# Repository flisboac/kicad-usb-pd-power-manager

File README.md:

# USB-PD Power Manager

This is a USB-PD-capable Battery Charger and Power Path Module based on the [HUSB238 USB-PD Sink Controller](https://www.hynetek.com/uploadfiles/site/219/news/aabbbbdb-48c9-4a44-a6dc-2c15f53282e6.pdf) and [BQ25672 Battery Charger](https://www.ti.com/lit/ds/symlink/bq25672.pdf).

> This is **NOT** a finished project!

## Objectives

The main objective with this module is, quite literally, to make the "perfect Power Manager module/solution for any project." Obviously, "perfect" here is what I consider perfect myself, so here goes a laundry list of things I want from it:

1. Actually negotiate power when powered through USB, whatever the means.
    - A lot of projects just depend on the common 5.1K resistor on CC1/CC2 to get 5V/3A, but that's not a guarantee unless your use-case is very restricted.
    - Also, pulling 500mA or more on USB without USB connection/negotiation, USB-PD or USB-BC is out of spec. Not that it matters in all projects, but a well behaved USB-powered solution avoids many surprises.
    - 5V is pretty ubiquitous, but some projects may necessitate more voltage to drive higher-powered devices (e.g. fans), or to charge batteries more efficiently. Higher voltages are also necessary in order for USB-C to deliver more power in general.
2. Capable of negotiating power through **USB PD**, up to the highest power profile available (100W, 20V @ 5A).
    - In the future, I'd like this to be expanded to support USB-PPS as well, but chip availability is a bit low for enabling this functionality, so USB-PD will do for the moment.
3. Capable of falling back to **USB BC**, if not connecting to USB Type-C end-to-end.
    - There's plenty of power available through USB BC 1.2 or similar charger protocols, and it's still very common to use previous USB-A or USB-B (i.e. non Type-C) ports in many places.
4. Battery-powered, with a battery charger built-in.
    - Necessitates Power Path management.
    - Also necessitates battery protection measures, e.g. overcurrent protection, overvoltage protection, reverse polarity protection, etc.
5. Have the smallest possible form-factor. Be friendly to breadboarding, while still being useful as a standalone module.
    - Size would be similar to a Raspberry Pi Pico in width, but no specific restriction on length.
    - Ahem... ✨ [Castellations!](https://jlcpcb.com/blog/castellated-pcbs-introduction-and-design-requirements) ✨ (What a word, ain't it?)
6. Guaranteed 5V and 3.3V outputs, regardless of the "mains" voltage.
    - 5V with a switched dc/dc regulator, for powering sensors, LEDs, etc. Optionally adjustable to 3.3V via standalone (pin) configuration.
    - 3.3V with a LDO for powering microcontrollers, also adjustable to 5V if needed (e.g. for less noise).
    - Both can be disabled at any time, to reduce power consumption.
7. Optional external power input, as a backup for USB power.
8. Battery fuel gauge built-in to the module.
    - Helps with power consumption prediction, etc.
9. I2C as the main control option, but standalone pin or jumper based configuration also possible.
    - Standalone controls enable the board to be used in scenarios without a microcontroller.
    - I2C enables the board to be used with higher precision (e.g. negotiate USB-PD power after first negotiation, configure current/charger limits past the default standalone ones, monitor power consumption, etc.)

I also wanted to put a soft-reset button. I like the idea of the module having power and reset buttons that are useable to a microcontroller, with e.g. long presses meaning turn-off/reset, etc. Perhaps that may be included in a future revision.

## Implementation

### Component selection

Focus on ICs from known brands. Easier to predict availability and quality.

Basic test: go to JLCPCB and see if there's a good amount of stock available. Discard any option with zero stock. Price also important, but not essential (as this will be a personal project).

- USB-PD Sink Controller (**VUSB**): [**HUSB238_002DD**](https://www.hynetek.com/uploadfiles/site/219/news/aabbbbdb-48c9-4a44-a6dc-2c15f53282e6.pdf)
    - 001DD or 004DD would be the best option, but the 002DD has a whole lot more availability for some reason.
    - VUSB is not supposed to be consumed directly, but instead it must be passed on to the Power Path controller.
    - VUSB is only switched on when USB-PD negotiation is performed (either with success or failure).
- Battery Charger and Power Path (**VSYS**): [**BQ25672**](https://www.ti.com/lit/ds/symlink/bq25672.pdf)
    - Selected mostly because of the 24V input voltage tolerance.
    - Having I2C is also important, but not essential.
    - Could be the BQ25792 as well, it's pin-compatible and offers more power, but the BQ25672 has better availability
- Switch-mode DC/DC converter (**VSW**): [**TPS63070**](https://www.ti.com/lit/ds/symlink/tps63070.pdf)
    - Being able to step-up is important for scenarios with 1-cell batteries, or when the input voltage is lower than the output voltage in general. Even more important is to be able to step-down the voltage, considering the upwards of 24V inputs. Hence, it must be a buck-boost.
    - Input comes from VSYS (BQ25672), which reduces the required VIN to 19V.
    - Unfortunately, it has a 16V input voltage limit, but it's the highest limit amongst the moderately available buck-boosts out there. I found no other buck-boost as available or as cheap as this one. If anyone knows of a better option PLEASE let me know, I researched quite a lot but couldn't find a better one!
    - Because of the low VIN input, the module can only be used with up to 3-cell configurations, which limits VSYS to around 13V max. Going above that risks damaging the buck-boost.
- Low-dropout voltage regulator (**VLDO**): [**TPS7A2601**](https://www.ti.com/lit/ds/symlink/tps7a26.pdf)
    - I quite like this LDO!
    - Current limit is a bit low at 500mA, but it's enough for most projects. Higher power can be better served by VBUS or VSW
    - Target output voltages: 3.3V and 5V.
    - Has a very high VIN, at 20V. Safe to connect to VBUS/VSYS, but not exactly safe to use at higher voltages (e.g. regulate from 20V VIN but with much lower output currents in order not to blow it up!)
- MOSFETs: focus on using dual mosfet ICs, in order to reduce board space usage whenever possible.
    - Dual N-Channel: [**Si7224DN**](https://www.mouser.com/datasheet/2/427/si7224dn-1764912.pdf)
        - One of the channels has a lower Vgs, kinda weird. Could have chosen a better one.
    - Dual P-Channel: [**Si7223DN**](https://www.vishay.com/docs/75609/si7223dn.pdf)
    - N-channel and P-channel: [**DMC3025LDV**](https://www.diodes.com/datasheet/download/DMC3025LDV.pdf)
    - Focus on packages compatible with DFN-3x3. Small enough for higher power, whilst being easier to find replacements later on (e.g. chinese options like the HSBB3313, HSBB3909, HSBB6254, HSBB3202, etc.)
    - There were probably better options out there, but I got tired of looking at some point...
- Battery fuel gauge: [**MAX17205G**](https://www.analog.com/media/en/technical-documentation/data-sheets/max17201-max17215.pdf)
    - No particular reason for choosing this one other than the fact that it supports at least 3-cell batteries.
    - Has good performance, low power consumption and enough availability.
    - Useful that it can balance cells as well!

### Module topology

The KiCad schematic focuses on showing the whole module as a single page. I like the idea of being able to see the whole circuit at a glance, obviously separated by smaller logical parts, but this may not be optimal in order to show the constituent parts of the schematic as a whole.

So, follows below a diagram making more evident the constituent parts of the module, I hope it makes sense:

### Schematics

[Schematics PDF here.](/docs/kicad/schematics/toy-usb-pd-power-manager.pdf)

### PCB layout

I stopped working on the PCB layout in order to re-evaluate the project and make a review in general, but all the constituent parts are laid out and routed (with some exceptions). For example, the switch-mode DC/DC converters are laid out according to datasheet suggestions, but are not connected to the overall board.

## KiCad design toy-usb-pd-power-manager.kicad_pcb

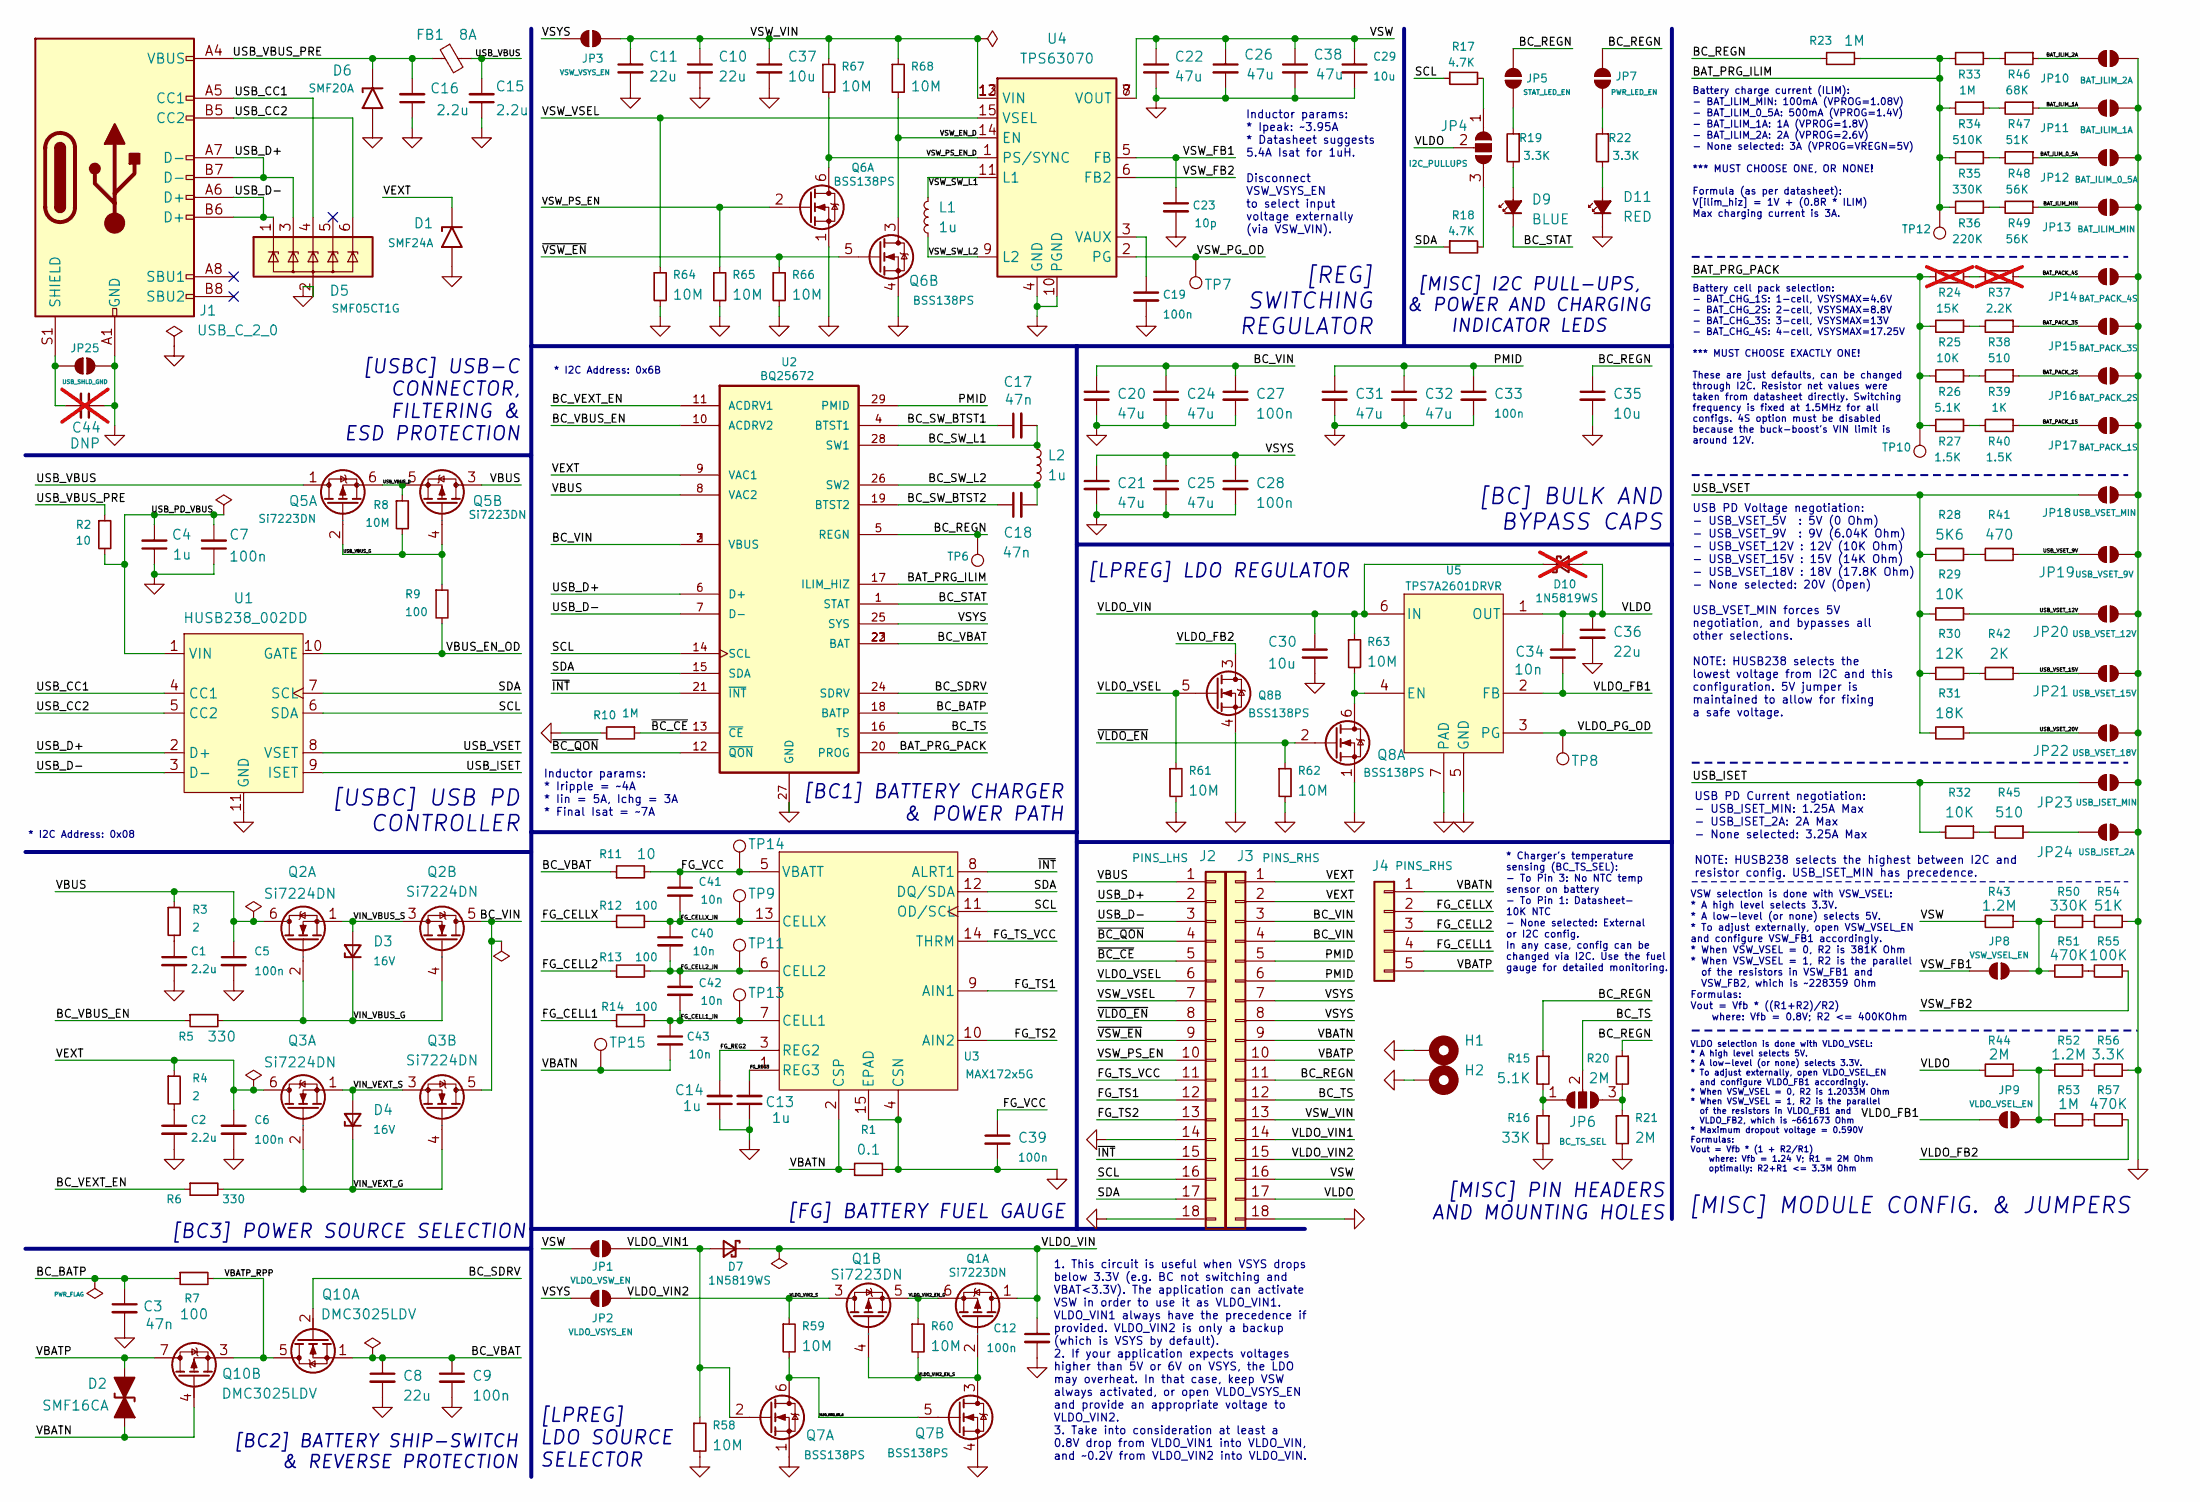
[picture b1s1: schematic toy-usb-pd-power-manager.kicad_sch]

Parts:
C1, C2: 2.2u; C_0805_2012Metric
C3, C17, C18: 47n; C_0402_1005Metric
C4, C13, C14: 1u; C_0402_1005Metric
C5, C6, C7, C9, C12, C19, C27, C28, C33, C39: 100n; C_0402_1005Metric
C8, C10, C11, C36: 22u; C_0805_2012Metric
C15, C16: 2.2u; C_0603_1608Metric
C20, C21, C22, C24, C25, C26, C31, C32, C38: 47u; C_0805_2012Metric
C23: 10p; C_0402_1005Metric
C29, C37: 10u; C_0603_1608Metric
C30, C35: 10u; C_0805_2012Metric
C34, C40, C41, C42, C43: 10n; C_0402_1005Metric
C44: DNP; C_0603_1608Metric; not fitted
D1: SMF24A; D_SMF
D2: SMF16CA; D_SOD-123F
D3, D4: 16V; D_SOD-523
D5: SMF05CT1G; SOT-23-6
D6: SMF20A; D_SMF
D7: 1N5819WS; D_SOD-323
D9: BLUE; LED_0603_1608Metric
D10: 1N5819WS; D_SOD-323; not fitted
D11: RED; LED_0603_1608Metric
FB1: 8A; L_1210_3225Metric
H1, H2: MountingHole_Pad; MountingHole_2.2mm_M2_DIN965_Pad_TopBottom
J1: USB_C_2_0; USB_C_Receptacle_GCT_USB4105-xx-A_16P_TopMnt_Horizontal
J2: PINS_LHS; PinHeader_1x18_P2.54mm_Vertical
J3: PINS_RHS; PinHeader_1x18_P2.54mm_Vertical
J4: PINS_RHS; PinHeader_1x05_P2.54mm_Vertical
JP1: VLDO_VSW_EN; SolderJumper-2_P1.3mm_Open_Pad1.0x1.5mm
JP2: VLDO_VSYS_EN; SolderJumper-2_P1.3mm_Open_Pad1.0x1.5mm
JP3: VSW_VSYS_EN; SolderJumper-2_P1.3mm_Open_Pad1.0x1.5mm
JP4: I2C_PULLUPS; SolderJumper-3_P1.3mm_Open_Pad1.0x1.5mm
JP5: STAT_LED_EN; SolderJumper-2_P1.3mm_Open_Pad1.0x1.5mm
JP6: BC_TS_SEL; SolderJumper-3_P1.3mm_Open_Pad1.0x1.5mm
JP7: PWR_LED_EN; SolderJumper-2_P1.3mm_Open_Pad1.0x1.5mm
JP8: VSW_VSEL_EN; SolderJumper-2_P1.3mm_Open_Pad1.0x1.5mm
JP9: VLDO_VSEL_EN; SolderJumper-2_P1.3mm_Open_Pad1.0x1.5mm
JP10: BAT_ILIM_2A; SolderJumper-2_P1.3mm_Open_Pad1.0x1.5mm
JP11: BAT_ILIM_1A; SolderJumper-2_P1.3mm_Open_Pad1.0x1.5mm
JP12: BAT_ILIM_0_5A; SolderJumper-2_P1.3mm_Open_Pad1.0x1.5mm
JP13: BAT_ILIM_MIN; SolderJumper-2_P1.3mm_Open_Pad1.0x1.5mm
JP14: BAT_PACK_4S; SolderJumper-2_P1.3mm_Open_Pad1.0x1.5mm
JP15: BAT_PACK_3S; SolderJumper-2_P1.3mm_Open_Pad1.0x1.5mm
JP16: BAT_PACK_2S; SolderJumper-2_P1.3mm_Open_Pad1.0x1.5mm
JP17: BAT_PACK_1S; SolderJumper-2_P1.3mm_Open_Pad1.0x1.5mm
JP18: USB_VSET_MIN; SolderJumper-2_P1.3mm_Open_Pad1.0x1.5mm
JP19: USB_VSET_9V; SolderJumper-2_P1.3mm_Open_Pad1.0x1.5mm
JP20: USB_VSET_12V; SolderJumper-2_P1.3mm_Open_Pad1.0x1.5mm
JP21: USB_VSET_15V; SolderJumper-2_P1.3mm_Open_Pad1.0x1.5mm
JP22: USB_VSET_18V; SolderJumper-2_P1.3mm_Open_Pad1.0x1.5mm
JP23: USB_ISET_MIN; SolderJumper-2_P1.3mm_Open_Pad1.0x1.5mm
JP24: USB_ISET_2A; SolderJumper-2_P1.3mm_Open_Pad1.0x1.5mm
JP25: USB_SHLD_GND; SolderJumper-2_P1.3mm_Open_Pad1.0x1.5mm
L1, L2: 1u; L_Changjiang_FXL0530
Q1, Q5: Si7223DN; Vishay_PowerPAK_1212-8_Dual
Q2, Q3: Si7224DN; Vishay_PowerPAK_1212-8_Dual
Q6, Q7, Q8: BSS138PS; SOT-363_SC-70-6
Q10: DMC3025LDV; Diodes_PowerDI3333-8_UXC_3.3x3.3mm_P0.65mm
R1: 0.1; R_1210_3225Metric
R2: 10; R_0402_1005Metric
R3: 2; R_0603_1608Metric
R4: 2; R_0402_1005Metric
R5, R6: 330; R_0402_1005Metric
R7, R9: 100; R_0402_1005Metric
R8, R58, R59, R60, R61, R62, R63, R64, R65, R66, R67, R68: 10M; R_0402_1005Metric
R10, R23, R33: 1M; R_0402_1005Metric
R11: 10; R_0603_1608Metric
R12, R13, R14: 100; R_0603_1608Metric
R15, R26: 5.1K; R_0402_1005Metric
R16: 33K; R_0402_1005Metric
R17, R18: 4.7K; R_0402_1005Metric
R19, R22: 3.3K; R_0402_1005Metric
R20, R21: 2M; R_0402_1005Metric
R24: 15K; R_0402_1005Metric; not fitted
R25: 10K; R_0402_1005Metric
R27, R40: 1.5K; R_0402_1005Metric
R28: 5K6; R_0402_1005Metric; LCSC C25908
R29: 10K; R_0402_1005Metric; LCSC C25744
R30: 12K; R_0402_1005Metric; LCSC C25752
R31: 18K; R_0402_1005Metric; LCSC C25762
R32: 10K; R_0402_1005Metric; LCSC C25908
R34: 510K; R_0402_1005Metric
R35: 330K; R_0402_1005Metric
R36: 220K; R_0402_1005Metric
R37: 2.2K; R_0402_1005Metric; not fitted
R38: 510; R_0402_1005Metric
R39: 1K; R_0402_1005Metric
R41: 470; R_0402_1005Metric; LCSC C25117
R42: 2K; R_0402_1005Metric; LCSC C4109
R43, R52: 1.2M; R_0402_1005Metric; LCSC C25741
R44: 2M; R_0402_1005Metric; LCSC C25741
R45: 510; R_0402_1005Metric; LCSC C25117
R46: 68K; R_0402_1005Metric
R47: 51K; R_0402_1005Metric
R48, R49: 56K; R_0402_1005Metric
R50: 330K; R_0402_1005Metric; LCSC C25741
R51, R57: 470K; R_0402_1005Metric; LCSC C25741
R53: 1M; R_0402_1005Metric; LCSC C25741
R54: 51K; R_0402_1005Metric; LCSC C25741
R55: 100K; R_0402_1005Metric; LCSC C25741
R56: 3.3K; R_0402_1005Metric; LCSC C25741
TP6, TP7, TP8, TP9, TP10, TP11, TP12, TP13, TP14, TP15: TestPoint; TestPoint_Pad_1.0x1.0mm
U1: HUSB238_002DD; DFN-10-1EP_3x3mm_P0.5mm_EP1.7x2.5mm; JLCPCB C7471904
U2: BQ25672; SPECIFIC_BQ25672RQMR; JLCPCB C3682029
U3: MAX172x5G; SPECIFIC_MAX172x5G_21-0137_T1433-2C_MXM
U4: TPS63070; SPECIFIC_TPS63070_RNM0015A
U5: TPS7A2601DRVR; SPECIFIC_TPS7A2601DRVR_NoThermalVias

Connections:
/BAT_ILIM_0_5A: JP12.1 (A), R48.1
/BAT_ILIM_1A: JP11.1 (A), R47.1
/BAT_ILIM_2A: JP10.1 (A), R46.1
/BAT_ILIM_MIN: JP13.1 (A), R49.1
/BAT_PACK_1S: JP17.1 (A), R40.1
/BAT_PACK_2S: JP16.1 (A), R39.1
/BAT_PACK_3S: JP15.1 (A), R38.1
/BAT_PACK_4S: JP14.1 (A), R37.1
/BAT_PRG_ILIM: R23.1, R33.2, R34.2, R35.2, R36.2, TP12.1, U2.17 (ILIM_HIZ)
/BAT_PRG_PACK: R24.2, R25.2, R26.2, R27.2, TP10.1, U2.20 (PROG)
/BC_BATP: C3.1, R7.1, U2.18 (BATP)
/BC_REGN: C35.1, J3.11, JP5.2 (B), JP7.2 (B), R15.1, R20.1, R23.2, TP6.1, U2.5 (REGN)
/BC_SDRV: Q10.2 (G), U2.24 (SDRV)
/BC_STAT: D9.1 (K), U2.1 (STAT)
/BC_SW_BTST1: C17.1, U2.4 (BTST1)
/BC_SW_BTST2: C18.1, U2.19 (BTST2)
/BC_SW_L1: C17.2, L2.1, U2.28 (SW1)
/BC_SW_L2: C18.2, L2.2, U2.26 (SW2)
/BC_TS: J3.12, JP6.2 (C), U2.16 (TS)
/BC_VBAT: C8.1, C9.1, Q10.1 (S), R11.1, U2.22 (BAT), U2.23 (BAT)
/BC_VBUS_EN: R5.1, U2.10 (ACDRV2)
/BC_VEXT_EN: R6.1, U2.11 (ACDRV1)
/BC_VIN: C20.1, C24.1, C27.1, J3.3, J3.4, Q2.5 (D), Q3.5 (D), U2.2 (VBUS), U2.3 (VBUS)
/FG_CELL1: J4.4, R14.1
/FG_CELL1_IN: C42.2, C43.1, R14.2, TP13.1, U3.7 (CELL1)
/FG_CELL2: J4.3, R13.1
/FG_CELL2_IN: C40.2, C42.1, R13.2, TP11.1, U3.6 (CELL2)
/FG_CELLX: J4.2, R12.1
/FG_CELLX_IN: C40.1, C41.2, R12.2, TP9.1, U3.13 (CELLX)
/FG_REG2: C14.2, U3.3 (REG2)
/FG_REG3: C13.2, U3.1 (REG3)
/FG_TS1: J2.12, U3.9 (AIN1)
/FG_TS2: J2.13, U3.10 (AIN2)
/FG_TS_VCC: J2.11, U3.14 (THRM)
/FG_VCC: C39.1, C41.1, R11.2, TP14.1, U3.5 (VBATT)
/PMID: C31.1, C32.1, C33.1, J3.5, J3.6, U2.29 (PMID)
/SCL: J2.16, R17.1, U1.6 (SDA), U2.14 (SCL), U3.11 (OD/SCL)
/SDA: J2.17, R18.1, U1.7 (SCL), U2.15 (SDA), U3.12 (DQ/SDA)
/USB_CC1: D5.4 (IO3), J1.A5 (CC1), U1.4 (CC1)
/USB_CC2: D5.6 (IO5), J1.B5 (CC2), U1.5 (CC2)
/USB_D+: D5.3 (IO2), J1.A7 (D-), J1.B7 (D-), J2.2, U1.2 (D+), U2.6 (D+)
/USB_D-: D5.1 (IO1), J1.A6 (D+), J1.B6 (D+), J2.3, U1.3 (D-), U2.7 (D-)
/USB_ISET: JP23.1 (A), R32.2, U1.9 (ISET)
/USB_PD_VBUS: C4.2, C7.2, R2.2, U1.1 (VIN)
/USB_VBUS: C15.2, FB1.2, Q5.1 (D)
/USB_VBUS_D: Q5.5 (S), Q5.6 (S), R8.1
/USB_VBUS_G: Q5.2 (G), Q5.4 (G), R8.2, R9.1
/USB_VBUS_PRE: C16.2, D6.1 (A1), FB1.1, J1.A4 (VBUS), J1.A9 (VBUS), J1.B4 (VBUS), J1.B9 (VBUS), R2.1
/USB_VSET: JP18.1 (A), R28.2, R29.2, R30.2, R31.2, U1.8 (VSET)
/USB_VSET_9V: JP19.1 (A), R41.1
/USB_VSET_12V: JP20.1 (A), R29.1
/USB_VSET_15V: JP21.1 (A), R42.1
/USB_VSET_20V: JP22.1 (A), R31.1
/VBATN: C43.2, D2.1 (A1), J3.9, J4.1, Q10.4 (G), R1.1, TP15.1, U3.2 (CSP)
/VBATP: D2.2 (A2), J3.10, J4.5, Q10.7 (D)
/VBATP_RPP: Q10.3 (S), Q10.5 (D), R7.2
/VBUS: C5.1, J2.1, Q2.6 (D), Q5.3 (D), R3.1, U2.8 (VAC2)
/VBUS_EN_OD: R9.2, U1.10 (GATE)
/VEXT: C6.1, D1.1 (A1), J3.1, J3.2, Q3.6 (D), R4.1, U2.9 (VAC1)
/VIN_VBUS_G: D3.1 (K), Q2.2 (G), Q2.4 (G), R5.2
/VIN_VBUS_S: D3.2 (A), Q2.1 (S), Q2.3 (S)
/VIN_VEXT_G: D4.1 (K), Q3.2 (G), Q3.4 (G), R6.2
/VIN_VEXT_S: D4.2 (A), Q3.1 (S), Q3.3 (S)
/VLDO: C34.1, C36.1, D10.2 (A), J3.17, JP4.2 (C), R44.2, U5.1 (OUT)
/VLDO_FB1: C34.2, JP9.1 (A), U5.2 (FB)
/VLDO_FB2: Q8.3 (D), R57.1
/VLDO_PG_OD: TP8.1, U5.3 (PG)
/VLDO_VIN: C12.1, C30.1, D7.1 (K), D10.1 (K), Q1.1 (D), R63.1, U5.6 (IN)
/VLDO_VIN1: D7.2 (A), J3.14, JP1.2 (B), Q7.2 (G), R58.1
/VLDO_VIN2: J3.15, JP2.2 (B), Q1.3 (D), R59.1
/VLDO_VIN2_EN_G: Q1.5 (S), Q1.6 (S), Q7.5 (G), Q7.6 (D), R59.2, R60.1
/VLDO_VIN2_EN_S: Q1.2 (G), Q1.4 (G), Q7.3 (D), R60.2
/VLDO_VSEL: J2.6, Q8.5 (G), R61.1
/VSW: C22.1, C26.1, C29.1, C38.1, J3.16, JP1.1 (A), R43.2, U4.7 (VOUT), U4.8 (VOUT)
/VSW_EN_D: Q6.3 (D), R68.2, U4.14 (EN)
/VSW_FB1: C23.1, JP8.1 (A), U4.5 (FB)
/VSW_FB2: R55.1, U4.6 (FB2)
/VSW_PG_OD: TP7.1, U4.2 (PG)
/VSW_PS_EN: J2.10, Q6.2 (G), R65.1
/VSW_PS_EN_D: Q6.6 (D), R67.2, U4.1 (PS/SYNC)
/VSW_SW_L1: L1.2, U4.11 (L1)
/VSW_SW_L2: L1.1, U4.9 (L2)
/VSW_VIN: C10.1, C11.1, C37.1, J3.13, JP3.2 (B), R67.1, R68.1, U4.12 (VIN), U4.13 (VIN)
/VSW_VSEL: J2.7, R64.1, U4.15 (VSEL)
/VSYS: C21.1, C25.1, C28.1, J3.7, J3.8, JP2.1 (A), JP3.1 (A), U2.25 (SYS)
/~BC_CE: J2.5, R10.1, U2.13 (~CE)
/~BC_QON: J2.4, U2.12 (~QON)
/~INT: J2.15, U2.21 (~INT), U3.8 (ALRT1)
/~VLDO_EN: J2.8, Q8.2 (G), R62.1
/~VSW_EN: J2.9, Q6.5 (G), R66.1
GND: C1.2, C2.2, C3.2, C4.1, C5.2, C6.2, C7.1, C8.2, C9.2, C10.2, C11.2, C12.2, C13.1, C14.1, C15.1, C16.1, C19.2, C20.2, C21.2, C22.2, C23.2, C24.2, C25.2, C26.2, C27.2, C28.2, C29.2, C30.2, C31.2, C32.2, C33.2, C35.2, C36.2, C37.2, C38.2, C39.2, C44.1, D1.2 (A2), D5.2 (GND), D6.2 (A2), D11.1 (K), H1.1, H2.1, J1.A1 (GND), J1.A12 (GND), J1.B1 (GND), J1.B12 (GND), J2.14, J2.18, J3.18, JP10.2 (B), JP11.2 (B), JP12.2 (B), JP13.2 (B), JP14.2 (B), JP15.2 (B), JP16.2 (B), JP17.2 (B), JP18.2 (B), JP19.2 (B), JP20.2 (B), JP21.2 (B), JP22.2 (B), JP23.2 (B), JP24.2 (B), JP25.2 (B), Q6.1 (S), Q6.4 (S), Q7.1 (S), Q7.4 (S), Q8.1 (S), Q8.4 (S), R1.2, R10.2, R16.2, R21.2, R54.1, R56.1, R58.2, R61.2, R62.2, R64.2, R65.2, R66.2, U1.11 (GND), U2.27 (GND), U3.4 (CSN), U3.15 (EPAD), U4.4 (GND), U4.10 (PGND), U5.5 (GND), U5.7 (PAD)
unnamed: C1.1, R3.2
unnamed: C2.1, R4.2
unnamed: D9.2 (A), R19.2
unnamed: D11.2 (A), R22.2
unnamed: C44.2, J1.S1 (SHIELD), JP25.1 (A)
unnamed: JP4.1 (A), R17.2
unnamed: JP4.3 (B), R18.2
unnamed: JP5.1 (A), R19.1
unnamed: JP6.1 (A), R15.2, R16.1
unnamed: JP6.3 (B), R20.2, R21.1
unnamed: JP7.1 (A), R22.1
unnamed: JP8.2 (B), R43.1, R50.2, R51.2
unnamed: JP9.2 (B), R44.1, R52.2, R53.2
unnamed: JP24.1 (A), R45.1
unnamed: Q8.6 (D), R63.2, U5.4 (EN)
unnamed: R24.1, R37.2
unnamed: R25.1, R38.2
unnamed: R26.1, R39.2
unnamed: R27.1, R40.2
unnamed: R28.1, R41.2
unnamed: R30.1, R42.2
unnamed: R32.1, R45.2
unnamed: R33.1, R46.2
unnamed: R34.1, R47.2
unnamed: R35.1, R48.2
unnamed: R36.1, R49.2
unnamed: R50.1, R54.2
unnamed: R51.1, R55.2
unnamed: R52.1, R56.2
unnamed: R53.1, R57.2
unnamed: C19.1, U4.3 (VAUX)

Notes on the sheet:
[BC3] POWER SOURCE SELECTION
USB PD Current negotiation: - USB_ISET_MIN: 1.25A Max - USB_ISET_2A: 2A Max - None selected: 3.25A Max NOTE: HUSB238 selects the highest between I2C and resistor config. USB_ISET_MIN has precedence.
[USBC] USB PD CONTROLLER
* I2C Address: 0x08
[BC1] BATTERY CHARGER & POWER PATH
[FG] BATTERY FUEL GAUGE
USB PD Voltage negotiation: - USB_VSET_5V : 5V (0 Ohm) - USB_VSET_9V : 9V (6.04K Ohm) - USB_VSET_12V : 12V (10K Ohm) - USB_VSET_15V : 15V (14K Ohm) - USB_VSET_18V : 18V (17.8K Ohm) - None selected: 20V (Open) USB_VSET_MIN forces 5V negotiation, and bypasses all other selections. NOTE: HUSB238 selec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
Battery cell pack selection: - BAT_CHG_1S: 1-cell, VSYSMAX=4.6V - BAT_CHG_2S: 2-cell, VSYSMAX=8.8V - BAT_CHG_3S: 3-cell, VSYSMAX=13V - BAT_CHG_4S: 4-cell, VSYSMAX=17.25V *** MUST CHOOSE EXACTLY ONE! These are just defaults, can be changed through I2C. Resistor net values were taken from datasheet d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
[BC2] BATTERY SHIP-SWITCH & REVERSE PROTECTION
[MISC] PIN HEADERS AND MOUNTING HOLES
Inductor params: * Ipeak: ~3.95A * Datasheet suggests 5.4A Isat for 1uH. Disconnect VSW_VSYS_EN to select input voltage externally (via VSW_VIN).
1. This circuit is useful when VSYS drops below 3.3V (e.g. BC not switching and VBAT<3.3V). The application can activate VSW in order to use it as VLDO_VIN1. VLDO_VIN1 always have the precedence if provided. VLDO_VIN2 is only a backup (which is VSYS by default). 2. If your application expects volta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
[LPREG] LDO REGULATOR
VLDO selection is done with VLDO_VSEL: * A high level selects 5V. * A low-level (or none) selects 3.3V. * To adjust externally, open VLDO_VSEL_EN and configure VLDO_FB1 accordingly. * When VSW_VSEL = 0, R2 is 1.2033M Ohm * When VSW_VSEL = 1, R2 is the parallel of the resistors in VLDO_FB1 and VLDO_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
[MISC] I2C PULL-UPS, & POWER AND CHARGING INDICATOR LEDS
VSW selection is done with VSW_VSEL: * A high level selects 3.3V. * A low-level (or none) selects 5V. * To adjust externally, open VSW_VSEL_EN and configure VSW_FB1 accordingly. * When VSW_VSEL = 0, R2 is 381K Ohm * When VSW_VSEL = 1, R2 is the parallel of the resistors in VSW_FB1 and VSW_FB2, whic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
* I2C Address: 0x6B
* Charger's temperature sensing (BC_TS_SEL): - To Pin 3: No NTC temp sensor on battery - To Pin 1: Datasheet- 10K NTC - None selected: External or I2C config. In any case, config can be changed via I2C. Use the fuel gauge for detailed monitoring.
Battery charge current (ILIM): - BAT_ILIM_MIN: 100mA (VPROG=1.08V) - BAT_ILIM_0_5A: 500mA (VPROG=1.4V) - BAT_ILIM_1A: 1A (VPROG=1.8V) - BAT_ILIM_2A: 2A (VPROG=2.6V) - None selected: 3A (VPROG=VREGN=5V) *** MUST CHOOSE ONE, OR NONE! Formula (as per datasheet): V[ilim_hiz] = 1V + (0.8R * ILIM) Max ch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
[MISC] MODULE CONFIG. & JUMPERS
[LPREG] LDO SOURCE SELECTOR
[BC] BULK AND BYPASS CAPS
Inductor params: * Iripple = ~4A * Iin = 5A, Ichg = 3A * Final Isat = ~7A
[USBC] USB-C CONNECTOR, FILTERING & ESD PROTECTION
[REG] SWITCHING REGULATOR

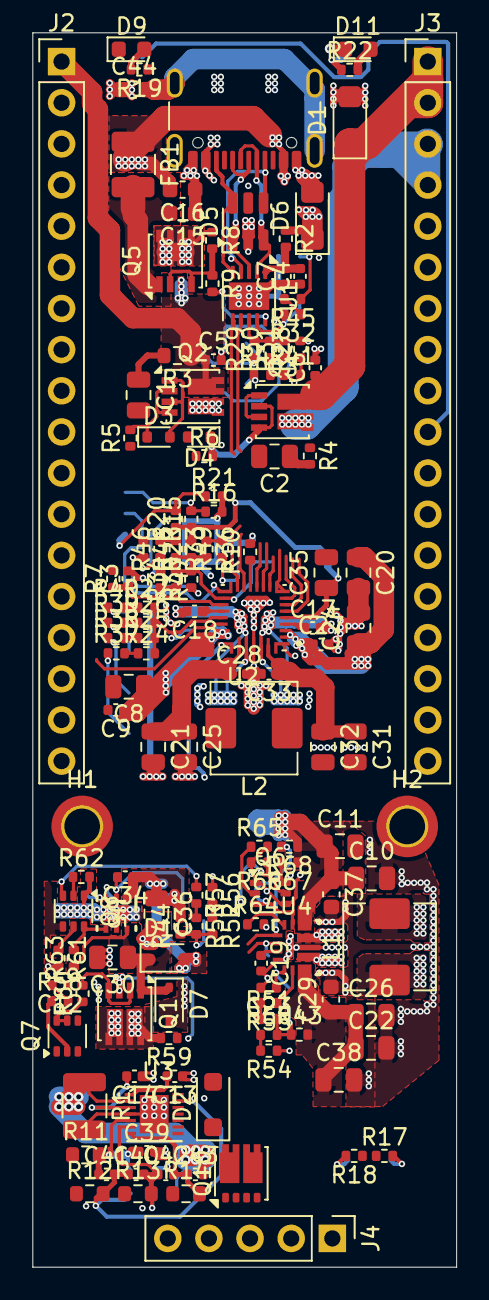
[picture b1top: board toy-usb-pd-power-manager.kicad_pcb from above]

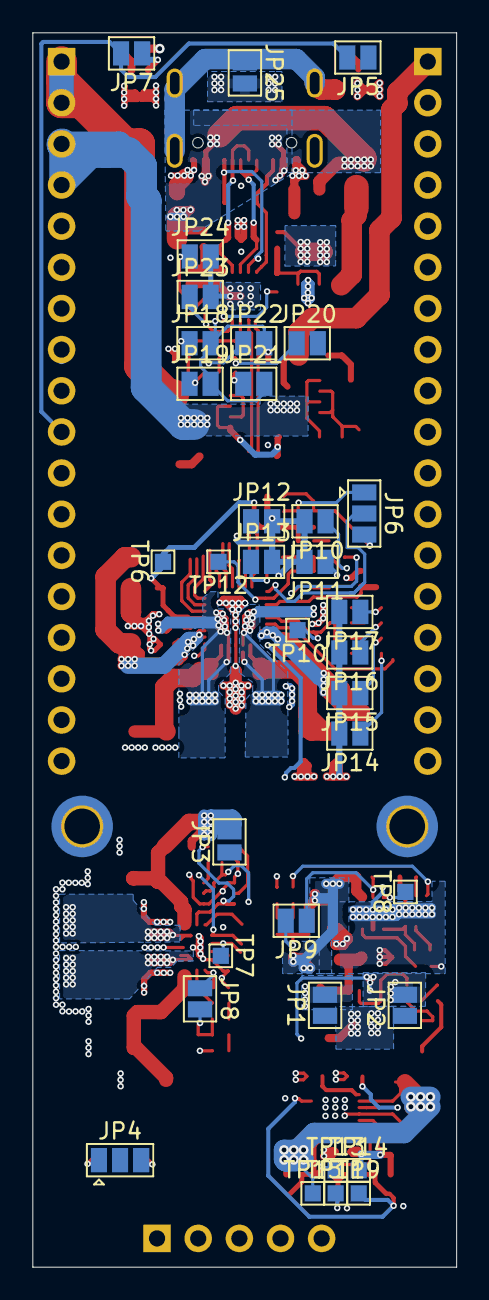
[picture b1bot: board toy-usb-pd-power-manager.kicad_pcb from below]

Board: 4 copper layers, 26.2 x 76.2 mm, 179 parts (35 on the bottom side), 122 nets.

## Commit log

2025-04-25 feat: initial schematic and first try on PCB
2025-04-29 refactor(pcb): improve positioning of ICs on the board
2025-04-29 feat: add README, diagrams and schematics
